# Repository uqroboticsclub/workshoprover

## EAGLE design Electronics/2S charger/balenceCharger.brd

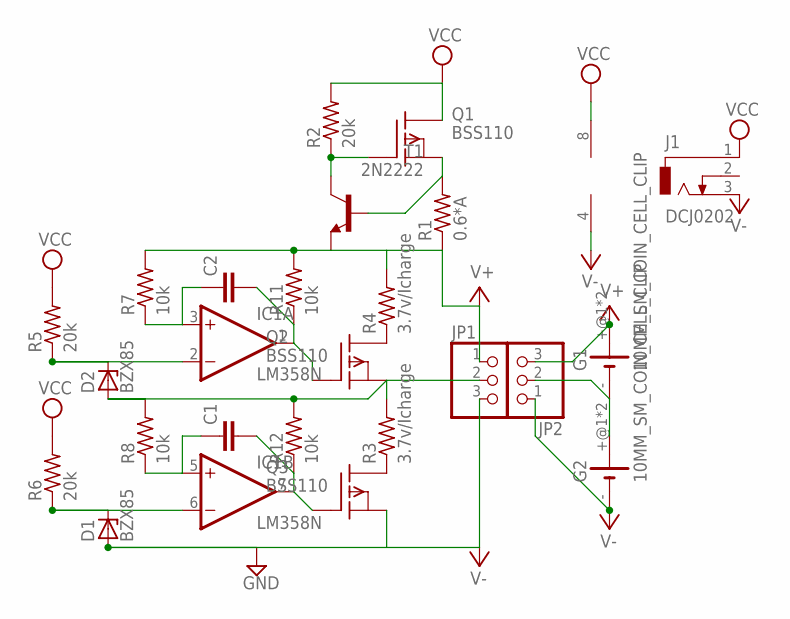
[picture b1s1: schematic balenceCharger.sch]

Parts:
C1, C2: C-EU025-060X050; C025-060X050
D1, D2: BZX85; DO41Z10
G1, G2: 10MM_SM_COIN_CELL_CLIP
IC1: LM358N; DIL08
J1: DCJ0202
JP1, JP2: PINHD-1X3/90; 1X03/90
Q1, Q2, Q3: BSS110; TO92
R1: 0.6*A; 0204/5
R2, R5, R6: 20k; 0204/5
R3, R4: 3.7v/Icharge; 0411V
R7, R8, R11, R12: 10k; 0204/5
T1: 2N2222; TO18

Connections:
GND: D1.A, JP1.3, Q3.1 (S)
unnamed: Q1.2 (G), R2.1, T1.3 (C)
unnamed: Q1.1 (S), R1.2, T1.2 (B)
unnamed: Q3.3 (D), R3.1
unnamed: D2.A, JP1.2, Q2.1 (S), R3.2, R8.2, R12.2
unnamed: Q2.3 (D), R4.1
unnamed: D2.C, IC1.2 (-IN), R5.1
unnamed: D1.C, IC1.6 (-IN), R6.1
unnamed: C2.1, IC1.3 (+IN), R7.1
unnamed: G1.-, G2.+@1 (+), G2.+@2 (+), JP2.2
unnamed: C1.1, IC1.5 (+IN), R8.1
unnamed: C1.2, IC1.7 (OUT), Q3.2 (G), R12.1
unnamed: C2.2, IC1.1 (OUT), Q2.2 (G), R11.1
V+: G1.+@1 (+), G1.+@2 (+), JP1.1, JP2.3, R1.1, R4.2, R7.2, R11.2, T1.1 (E)
V-: G2.-, IC1.4 (V-), J1.3, JP2.1
VCC: IC1.8 (V+), J1.1, Q1.3 (D), R2.2, R5.2, R6.2

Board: 2 copper layers, 24 parts (0 on the bottom side), 16 nets, no tracks yet.

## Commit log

2016-03-03 initial git
2016-03-13 simple 2s charger
    doesn't have correct components, still need to double check layout.
2016-03-13 remove lck
2016-03-13 error correction
2016-03-13 remove unwanted files
